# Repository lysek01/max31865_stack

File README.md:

# MAX31865 Stack

A stackable carrier board for the **Adafruit MAX31865** RTD-to-digital
converter. Each board hosts up to **8 MAX31865 modules** and multiple boards
can be stacked on brass standoffs to scale the channel count without changing
the wiring to the host.

## Overview

Each MAX31865 from Adafruit is an excellent PT100/PT1000 front-end, but
wiring more than a handful of them by hand is tedious and error-prone — every
module needs power, an SPI bus and its own chip-select line.

This project solves that with a carrier PCB that:

- mounts up to **8 plug-in MAX31865 modules** per board,
- brings out a **4-pin pluggable terminal block** per channel for the RTD
  sensor (2/3/4-wire compatible),
- shares one SPI bus across all modules,
- generates individual chip-select signals from a single **PCF8574 I2C
  expander**, so only a handful of signals (SDA, SCL, MOSI, MISO, SCK plus
  3.3 V/GND) ever leave the stack regardless of how many boards are stacked,
- **stacks vertically** on brass M3 standoffs through stackable pin headers
  that pass the bus straight through, so the wiring from the Raspberry Pi
  goes to a single **8-pin JST XH** connector on the bottom board and every
  board above it is simply plugged into the one below.

With the default I2C address range (0x20–0x27) the stack supports
**up to 8 boards = 64 RTD channels** from a single Raspberry Pi.

## Features

- Up to **8 channels per board**, scalable to **64 channels** per stack.
- Pluggable green terminal blocks for each sensor — sensors can be swapped
  without unsoldering or disturbing the stack.
- **2-, 3- and 4-wire RTD** wiring supported (selected per-module on the
  Adafruit board itself).
- Works with both **PT100** and **PT1000** modules; selectable in software.
- Connects to the host with a single **8-pin JST XH** cable on the bottom
  board; the rest of the stack is bussed through stackable pin headers.
- KiCad sources and JLCPCB production files included.
- Reference Python driver included that auto-detects expanders and modules,
  reads all channels in continuous mode and prints fault-decoded
  measurements.

## Hardware

### Block diagram

```
                              JST XH 8-pin
                                   │
                                   ▼
  Raspberry Pi ──── Board #1 (bottom) ──┐
                    Board #2            │  stacked through
                    Board #N            │  pass-through pin headers
                    ──────────────────  ┘  (I2C + SPI + power)
                         │
        ┌────────────────┼────────────────┐
        ▼                ▼                ▼
     PCF8574          PCF8574          PCF8574
      0x25             0x26             0x27
        │                │                │
        ▼                ▼                ▼
     8x CS            8x CS            8x CS
        │                │                │
        ▼                ▼                ▼
    8x MAX31865      8x MAX31865      8x MAX31865

  SPI bus (SCK, MOSI, MISO) is shared across every MAX31865 on every board.
  CS for each module is driven by one PCF8574 output.
```

The PCF8574 expander on each board takes the I2C address selected by the
jumpers `JP1` / `JP2` / `JP3` (PCF8574 address bits A0/A1/A2). This is how
each board in the stack gets its own unique address — and therefore its own
set of 8 chip-select lines.

### Per-board contents

| Reference | Part |
|-----------|------|
| U1        | PCF8574 I2C 8-bit I/O expander (SOIC-16) |
| 8x        | Sockets for Adafruit MAX31865 PT100/PT1000 breakout |
| 8x        | 4-pin pluggable terminal blocks (5.08 mm, RTD sensor) |
| JP1–JP3   | I2C address jumpers (A0, A1, A2) |
| J1        | 8-pin JST XH connector (host link, populated on bottom board only) |
| —         | 8-pin stackable pin headers — bus pass-through between boards |

### Stacking

Boards stack mechanically on **brass M3 standoffs** and electrically through
**stackable 8-pin pin headers**, which pass the I2C, SPI and power signals
straight up through the stack.

The bottom board carries the **8-pin JST XH connector (J1)** that is wired
to the Raspberry Pi. Any boards above it inherit the same bus through the
pass-through headers — no extra cabling is needed when adding a board.

Each board only needs a unique PCF8574 address, set with the three address
jumpers (`JP1`/`JP2`/`JP3`).

### Sensor wiring

Each channel exposes a 4-pin pluggable terminal block matching the Adafruit
MAX31865 module pinout. Use the Adafruit module's own solder jumpers to
configure 2-, 3- or 4-wire mode.

> ⚠️ Use a **reference resistor matched to your RTD**:
> - PT100  → 430 Ω  (default on Adafruit boards)
> - PT1000 → 4300 Ω
>
> Mixing PT1000 sensors with the default 430 Ω reference (or vice versa)
> will not work correctly.

## Connecting to a Raspberry Pi

The bottom board of the stack carries an **8-pin JST XH connector (J1)**
that links the whole stack to the Raspberry Pi. Each pin of the connector is
labelled on the board's silkscreen — wire each labelled signal to the
matching Raspberry Pi GPIO header pin according to the table below.

The diagram below highlights the relevant pin groups on the 40-pin header:
the **I²C** group (SDA / SCL) and the **SPI** group (MOSI / MISO / SCLK,
together with the 3V3 and GND pins that are convenient to use for powering
the stack).

Counting from the **left edge** of the JST XH connector (pin 1) to the
right (pin 8):

| JST pin | Silkscreen   | Function                | RPi physical pin | RPi BCM GPIO |
|:-------:|:------------:|:------------------------|:----------------:|:------------:|
| 1       | `GND`        | Ground                  | 6                | —            |
| 2       | `GND`        | Ground (redundant)      | any GND          | —            |
| 3       | `SDA`        | I²C data (PCF8574)      | 3                | GPIO 2       |
| 4       | `SCL`        | I²C clock (PCF8574)     | 5                | GPIO 3       |
| 5       | `MOSI`       | SPI MOSI (MAX31865)     | 19               | GPIO 10      |
| 6       | `MISO`       | SPI MISO (MAX31865)     | 21               | GPIO 9       |
| 7       | `CLK`        | SPI clock (MAX31865)    | 23               | GPIO 11      |
| 8       | `VCC`        | Logic supply            | 1 (3V3)          | —            |

Both `GND` pins on the connector (pins 1 and 2) are tied to the same ground
net on the board. In practice you only need to wire one of them on your
cable — the other can be left unconnected or used as a spare.

> ℹ️ The Adafruit MAX31865 breakout accepts 3 V–5 V on `VIN`, but its logic
> level must match `VIN`. When wiring to a Raspberry Pi (3.3 V GPIO), power
> the stack from the Pi's **3V3** pin — that keeps `VCC` and the SPI / I²C
> logic at the same level and matches the GPIO directly without a level
> shifter.

> ℹ️ The "RPi physical pin" column uses the 1–40 header numbering printed
> on Raspberry Pi pinout cards. "BCM GPIO" is the numbering reported by
> `pinout` and used in `/sys/class/gpio`. Both refer to the same physical
> pad; pick whichever is more convenient.

When more than one board is in the stack, the same signals propagate
upwards through the stackable pin headers — only this single JST cable goes
to the Pi.

## Software

A reference reader is provided in [`software/read.py`](software/read.py).
It runs on Linux (tested on Raspberry Pi OS) and:

1. Scans I2C addresses 0x20–0x27 for PCF8574 expanders.
2. For every CS pin on every expander, probes for a MAX31865 by writing and
   reading back the CONFIG and threshold registers.
3. Starts continuous conversion on every detected module.
4. Periodically reads all channels, decodes any fault bits, converts the raw
   ADC value to resistance and then to temperature using the
   **Callendar–Van Dusen** equation (closed-form for t ≥ 0 °C, bisection of
   the full 4-coefficient form for t < 0 °C).

### Requirements

- Raspberry Pi (or another Linux SBC) with I2C and SPI enabled
- Python 3.7+
- Python packages listed in [`software/requirements.txt`](software/requirements.txt):
  ```bash
  pip install -r software/requirements.txt
  ```

### Enabling I2C and SPI on Raspberry Pi

Both buses are disabled by default on a fresh Raspberry Pi OS image. Enable
them with `raspi-config`:

```bash
sudo raspi-config
```

Then navigate to **Interface Options → I2C → Enable** and
**Interface Options → SPI → Enable**, and reboot.

After the reboot you should see the devices in `/dev`:

```bash
ls /dev/i2c-* /dev/spidev*
# /dev/i2c-1  /dev/spidev0.0  /dev/spidev0.1
```

A quick sanity check that the boards are visible on the I2C bus:

```bash
sudo apt install i2c-tools
i2cdetect -y 1
```

You should see the PCF8574 expanders show up in the 0x20–0x27 range — one
address per board in the stack.

### Configuration

Open [`software/read.py`](software/read.py) and adjust the constants at the
top of the file:

| Constant            | Meaning                                                      |
|---------------------|--------------------------------------------------------------|
| `I2C_BUS`           | I2C bus index (`1` on Raspberry Pi)                          |
| `SPI_BUS`/`SPI_DEVICE` | SPI bus/CS index used to talk to the modules              |
| `SPI_SPEED_HZ`      | SPI clock; 100 kHz is conservative and reliable              |
| `THREE_WIRE`        | `True` for 3-wire RTDs, `False` for 2/4-wire                 |
| `FILTER_50HZ`       | `True` in 50 Hz mains regions, `False` for 60 Hz             |
| `RNOMINAL`          | `100.0` for PT100, `1000.0` for PT1000                       |
| `DEFAULT_RREF`      | Reference resistor on the Adafruit module (430 / 4300 Ω)     |
| `PRINT_INTERVAL`    | Seconds between measurement scans                            |

### Running

```bash
python3 software/read.py
```

Example output:

```
MAX31865 multi-board reader
==========================
I2C bus:       1
SPI bus/dev:   0.0
...

Scanning for PCF8574 expanders...
  expander found: 0x25
  expander found: 0x26
  expander found: 0x27

Detecting MAX31865 modules behind each CS pin...
Expander 0x25:
  P0: MAX31865 OK      CONFIG OK 0x91, marker OK
  ...

============================================================
2026-05-15 14:23:01
CH00 E0x25-P0: OK        23.451 C   R=109.123 Ohm   raw=8412
CH01 E0x25-P1: OK        23.802 C   R=109.260 Ohm   raw=8423
...
scan time: 142.318 ms   OK=24   NOT_OK=0
```

## Repository layout

```
.
├── assets/         photos of the assembled stack
├── hardware/       KiCad project (schematic, PCB) + JLCPCB production files
├── software/       Python reader for Raspberry Pi
├── LICENSE         MIT
└── README.md       you are here
```

## License

Released under the [MIT License](LICENSE). The Adafruit MAX31865 module is a
separate product; consult Adafruit's own documentation and licensing for the
module itself.

## Author

Martin Lysek — 2026.

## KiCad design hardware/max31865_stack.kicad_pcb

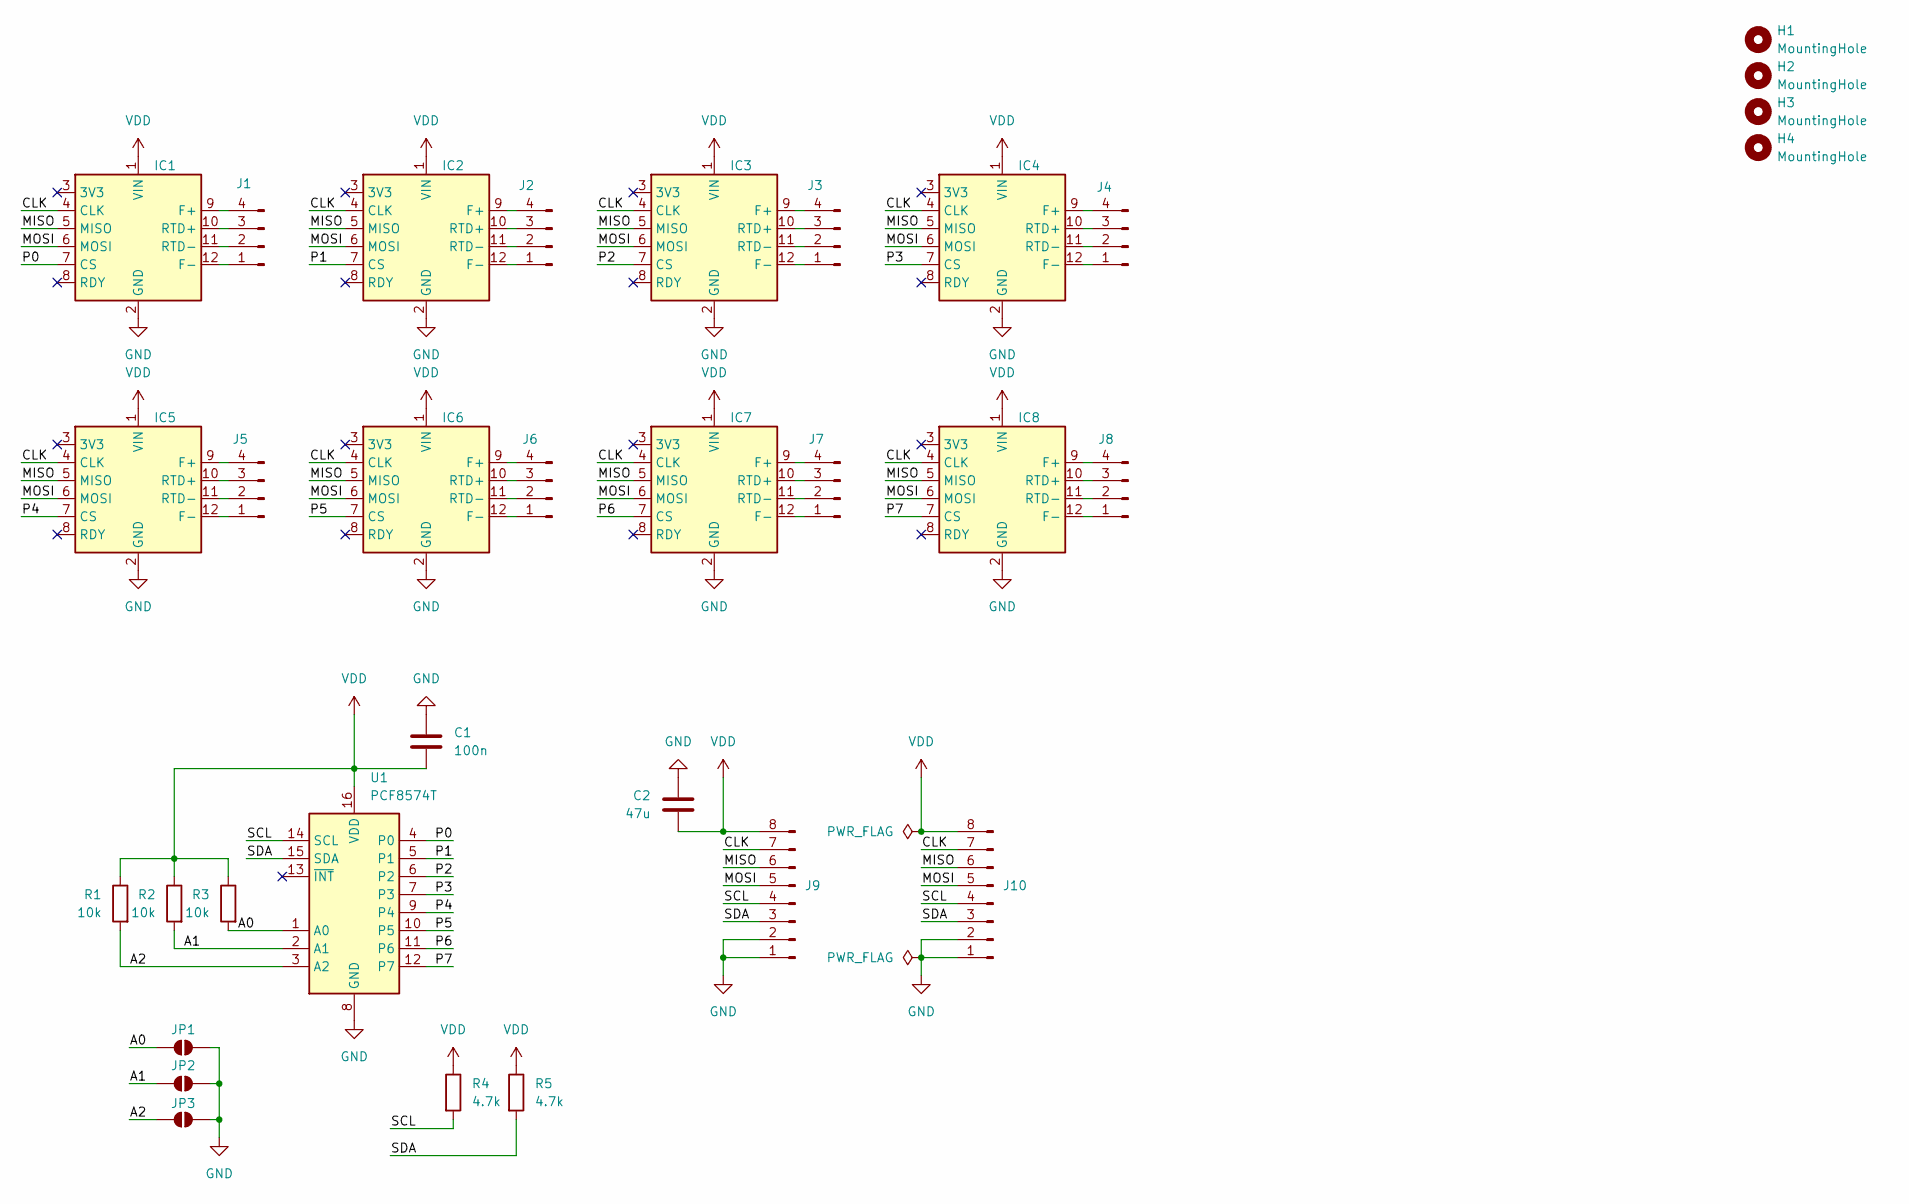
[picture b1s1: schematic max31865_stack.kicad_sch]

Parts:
C1: 100n; C_0603_1608Metric
C2: 47u; C_Radial_D5.0mm_H7.0mm_P2.00mm
H1, H2, H3, H4: MountingHole; MountingHole_3.2mm_M3
IC1, IC2, IC3, IC4, IC5, IC6, IC7, IC8: MAX31865; Adafruit_MAX31865
J1, J2, J3, J4, J5, J6, J7, J8: Conn_01x04_Pin; PhoenixContact_MSTBA_2,5_4-G-5,08_1x04_P5.08mm_Horizontal
J9, J10: Conn_01x08_Pin; PinHeader_1x08_P2.54mm_Vertical
JP1, JP2, JP3: SolderJumper_2_Open; SolderJumper-2_P1.3mm_Open_TrianglePad1.0x1.5mm
R1, R2, R3: 10k; R_0603_1608Metric
R4, R5: 4.7k; R_0603_1608Metric
U1: PCF8574T; SOIC-16W_7.5x10.3mm_P1.27mm

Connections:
/A0: JP1.1 (A), R3.2, U1.1 (A0)
/A1: JP2.1 (A), R2.2, U1.2 (A1)
/A2: JP3.1 (A), R1.2, U1.3 (A2)
/CLK: IC1.4 (CLK), IC2.4 (CLK), IC3.4 (CLK), IC4.4 (CLK), IC5.4 (CLK), IC6.4 (CLK), IC7.4 (CLK), IC8.4 (CLK), J9.7, J10.7
/MISO: IC1.5 (MISO), IC2.5 (MISO), IC3.5 (MISO), IC4.5 (MISO), IC5.5 (MISO), IC6.5 (MISO), IC7.5 (MISO), IC8.5 (MISO), J9.6, J10.6
/MOSI: IC1.6 (MOSI), IC2.6 (MOSI), IC3.6 (MOSI), IC4.6 (MOSI), IC5.6 (MOSI), IC6.6 (MOSI), IC7.6 (MOSI), IC8.6 (MOSI), J9.5, J10.5
/P0: IC1.7 (CS), U1.4 (P0)
/P1: IC2.7 (CS), U1.5 (P1)
/P2: IC3.7 (CS), U1.6 (P2)
/P3: IC4.7 (CS), U1.7 (P3)
/P4: IC5.7 (CS), U1.9 (P4)
/P5: IC6.7 (CS), U1.10 (P5)
/P6: IC7.7 (CS), U1.11 (P6)
/P7: IC8.7 (CS), U1.12 (P7)
/SCL: J9.4, J10.4, R4.2, U1.14 (SCL)
/SDA: J9.3, J10.3, R5.2, U1.15 (SDA)
GND: C1.1, C2.1, IC1.2 (GND), IC2.2 (GND), IC3.2 (GND), IC4.2 (GND), IC5.2 (GND), IC6.2 (GND), IC7.2 (GND), IC8.2 (GND), J9.1, J9.2, J10.1, J10.2, JP1.2 (B), JP2.2 (B), JP3.2 (B), U1.8 (GND)
unnamed: IC1.9 (F+), J1.4
unnamed: IC1.12 (F-), J1.1
unnamed: IC1.10 (RTD+), J1.3
unnamed: IC1.11 (RTD-), J1.2
unnamed: IC2.9 (F+), J2.4
unnamed: IC2.12 (F-), J2.1
unnamed: IC2.10 (RTD+), J2.3
unnamed: IC2.11 (RTD-), J2.2
unnamed: IC3.9 (F+), J3.4
unnamed: IC3.12 (F-), J3.1
unnamed: IC3.10 (RTD+), J3.3
unnamed: IC3.11 (RTD-), J3.2
unnamed: IC4.9 (F+), J4.4
unnamed: IC4.12 (F-), J4.1
unnamed: IC4.10 (RTD+), J4.3
unnamed: IC4.11 (RTD-), J4.2
unnamed: IC5.9 (F+), J5.4
unnamed: IC5.12 (F-), J5.1
unnamed: IC5.10 (RTD+), J5.3
unnamed: IC5.11 (RTD-), J5.2
unnamed: IC6.9 (F+), J6.4
unnamed: IC6.12 (F-), J6.1
unnamed: IC6.10 (RTD+), J6.3
unnamed: IC6.11 (RTD-), J6.2
unnamed: IC7.9 (F+), J7.4
unnamed: IC7.12 (F-), J7.1
unnamed: IC7.10 (RTD+), J7.3
unnamed: IC7.11 (RTD-), J7.2
unnamed: IC8.9 (F+), J8.4
unnamed: IC8.12 (F-), J8.1
unnamed: IC8.10 (RTD+), J8.3
unnamed: IC8.11 (RTD-), J8.2
VDD: C1.2, C2.2, IC1.1 (VIN), IC2.1 (VIN), IC3.1 (VIN), IC4.1 (VIN), IC5.1 (VIN), IC6.1 (VIN), IC7.1 (VIN), IC8.1 (VIN), J9.8, J10.8, R1.1, R2.1, R3.1, R4.1, R5.1, U1.16 (VDD)

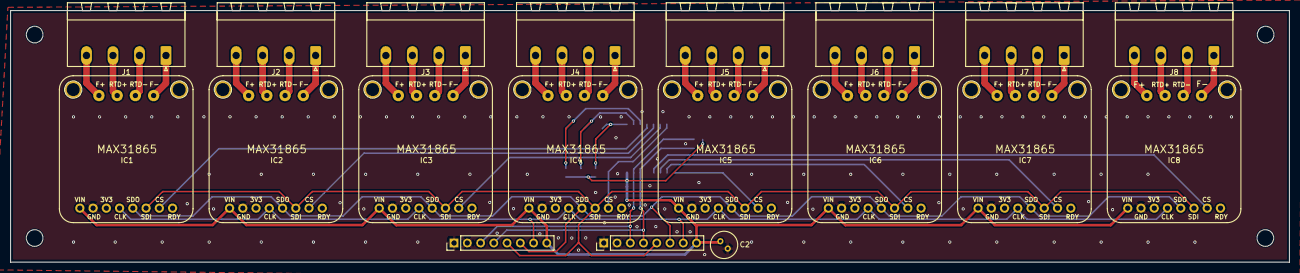
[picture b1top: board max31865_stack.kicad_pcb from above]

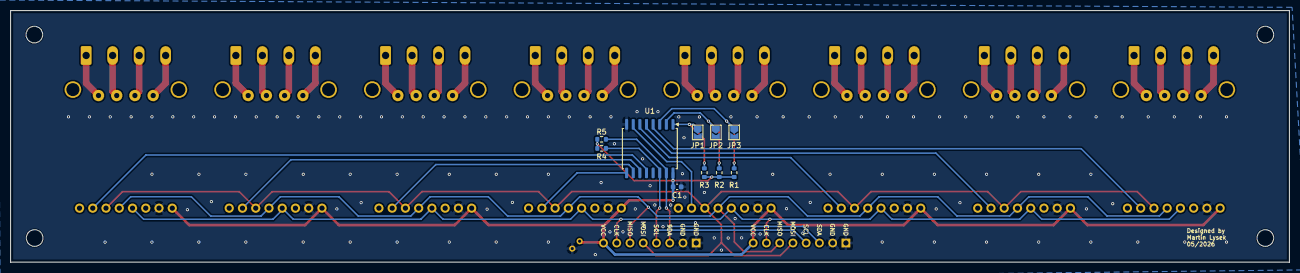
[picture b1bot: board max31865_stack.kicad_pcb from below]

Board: 2 copper layers, 245.2 x 48.2 mm, 33 parts (10 on the bottom side), 50 nets.

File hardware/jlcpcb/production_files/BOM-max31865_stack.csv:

Comment,Designator,Footprint,LCSC,Quantity
PCF8574T,U1,SOIC-16W_7.5x10.3mm_P1.27mm,,1
Conn_01x08_Pin,J10,PinHeader_1x08_P2.54mm_Vertical,,1
Conn_01x04_Pin,J8,"PhoenixContact_MSTBA_2,5_4-G-5,08_1x04_P5.08mm_Horizontal",,1
Conn_01x04_Pin,J7,"PhoenixContact_MSTBA_2,5_4-G-5,08_1x04_P5.08mm_Horizontal",,1
Conn_01x04_Pin,J6,"PhoenixContact_MSTBA_2,5_4-G-5,08_1x04_P5.08mm_Horizontal",,1
Conn_01x04_Pin,J5,"PhoenixContact_MSTBA_2,5_4-G-5,08_1x04_P5.08mm_Horizontal",,1
Conn_01x04_Pin,J4,"PhoenixContact_MSTBA_2,5_4-G-5,08_1x04_P5.08mm_Horizontal",,1
Conn_01x04_Pin,J3,"PhoenixContact_MSTBA_2,5_4-G-5,08_1x04_P5.08mm_Horizontal",,1
Conn_01x04_Pin,J2,"PhoenixContact_MSTBA_2,5_4-G-5,08_1x04_P5.08mm_Horizontal",,1
Conn_01x04_Pin,J1,"PhoenixContact_MSTBA_2,5_4-G-5,08_1x04_P5.08mm_Horizontal",,1
Conn_01x08_Pin,J9,PinHeader_1x08_P2.54mm_Vertical,,1
MAX31865,IC1,Adafruit_MAX31865,,1
MAX31865,IC2,Adafruit_MAX31865,,1
MAX31865,IC7,Adafruit_MAX31865,,1
MAX31865,IC5,Adafruit_MAX31865,,1
MAX31865,IC3,Adafruit_MAX31865,,1
MAX31865,IC4,Adafruit_MAX31865,,1
MAX31865,IC8,Adafruit_MAX31865,,1
MAX31865,IC6,Adafruit_MAX31865,,1
4.7k,R5,R_0603_1608Metric,,1
4.7k,R4,R_0603_1608Metric,,1
100n,C1,C_0603_1608Metric,,1
10k,R2,R_0603_1608Metric,,1
47u,C2,C_Radial_D5.0mm_H7.0mm_P2.00mm,,1
10k,R1,R_0603_1608Metric,,1
10k,R3,R_0603_1608Metric,,1

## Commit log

2026-05-14 initial
2026-05-15 README update
